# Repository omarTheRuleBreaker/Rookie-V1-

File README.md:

# Rookie-V1
Hi, I am making a cool Custom Keyboard from scratch, by myself

This is my custom 65% Alice layout keyboard that I’m designing from scratch. I started with watching some YOUTUBE videos and also took some help of AI for boosting up my Knowledge.

then I worked on schematic of the keyboard matrix, diodes, switches,  OLED display, Joystick, and the other components.
After finishing the schematic, I moved on to designing the PCB. I arranged the components, worked on the routing, and checked the connections and DRC errors to make sure everything was correct.

This project is helping me learn more about PCB design, KiCad, and how a keyboard actually works from the schematic to the final PCB.

### WHAT I LEARNED
Not gonna lie I learned many things it was a life time experience and next time I make an PCB for some other project it's  gonna be easy for me I learned shortcuts that will save me time and also made some friend's on SLACK that helped me , 
also #SHOUTOUT to @Flyingfish he saved me some time AND also THX to them who were  part of my journey.
- Here's what I really learned :
  
I learned how to turn a keyboard schematic into a proper PCB and how important it is to check every connection before moving forward. I also learned how to arrange components properly, route traces, use vias, and fix DRC errors in KiCad. Working on this project helped me understand more about PCB design and how all the different parts of a keyboard connect and work together.
gracias!

#### NOTE :-
If u want step by step PROCESS to make a simple easy Keyboard which include's Everything, SO just follow the  #### KEEB DOCS
HERE'S THE LINKE { https://keeb.hackclub.com/docs/getting-started/ }

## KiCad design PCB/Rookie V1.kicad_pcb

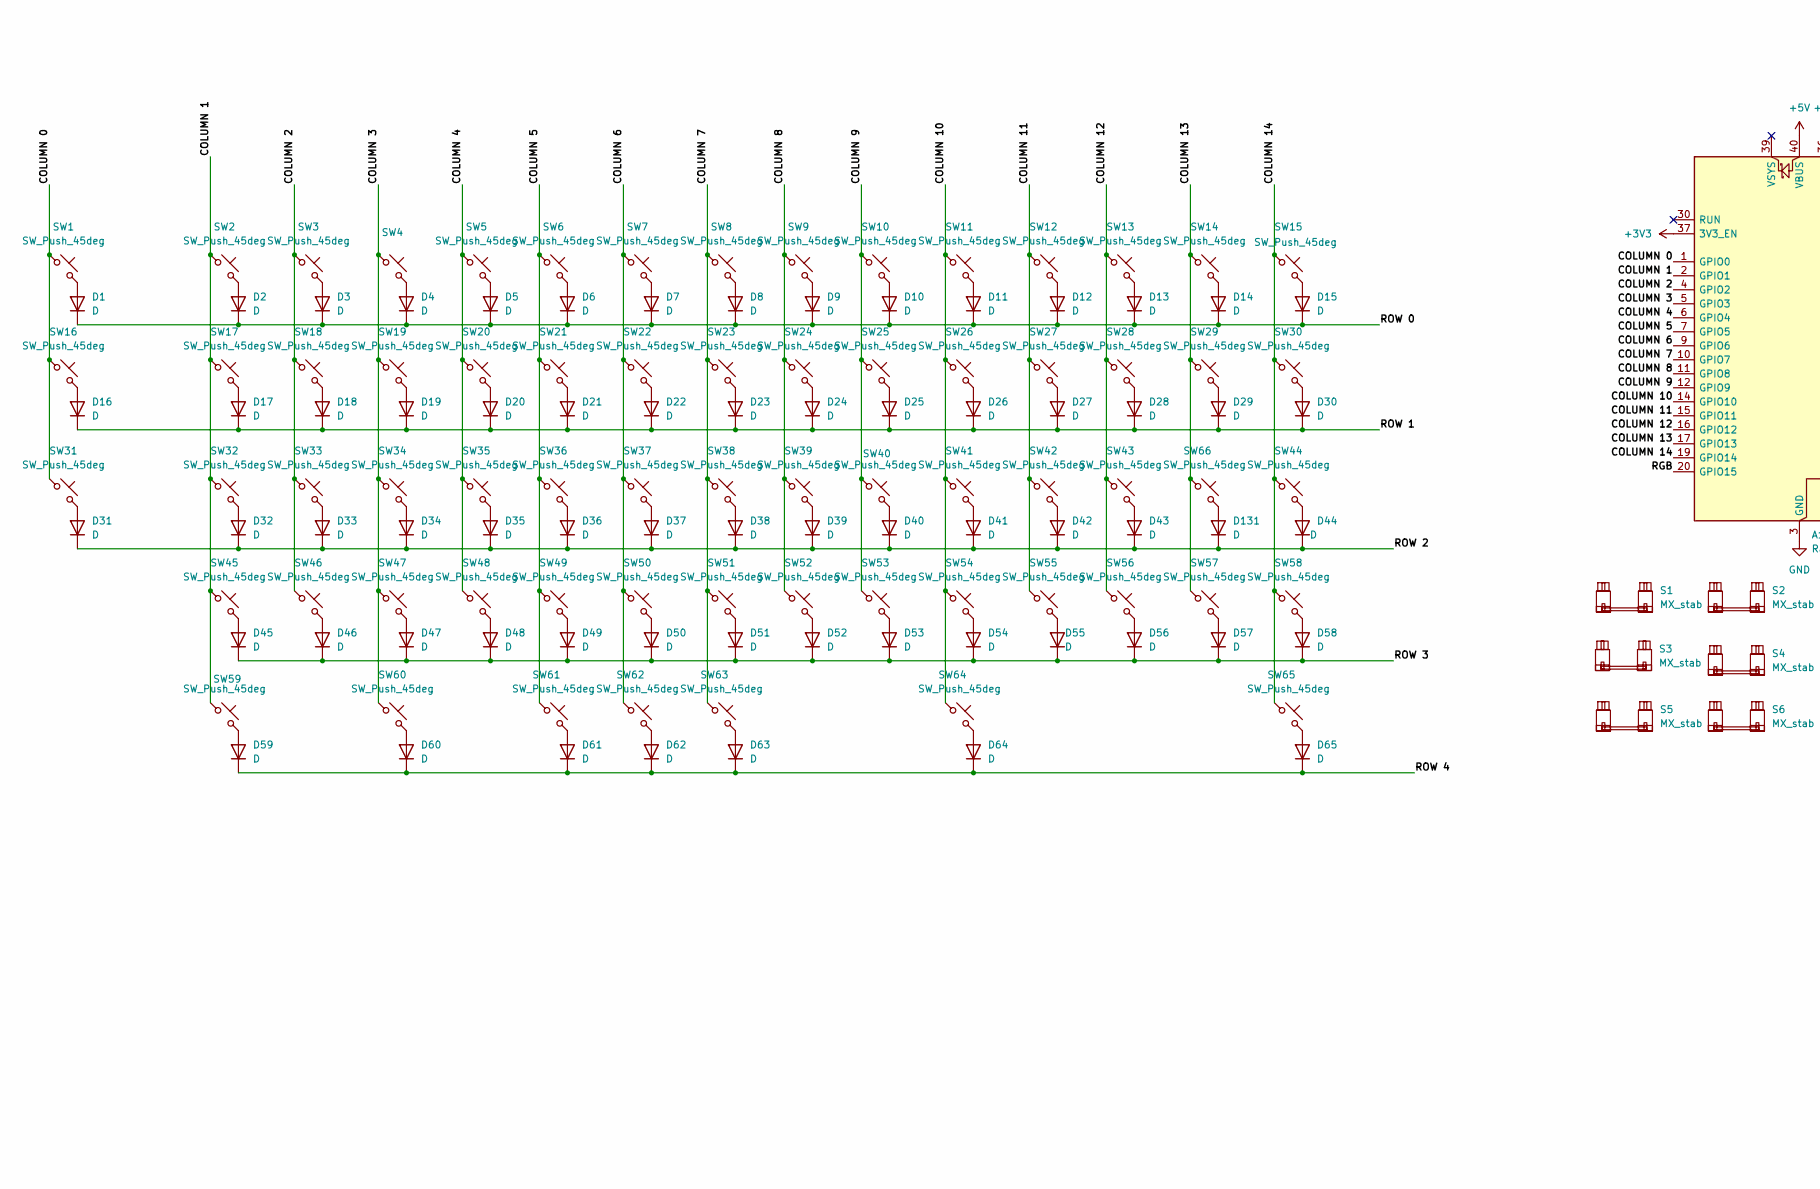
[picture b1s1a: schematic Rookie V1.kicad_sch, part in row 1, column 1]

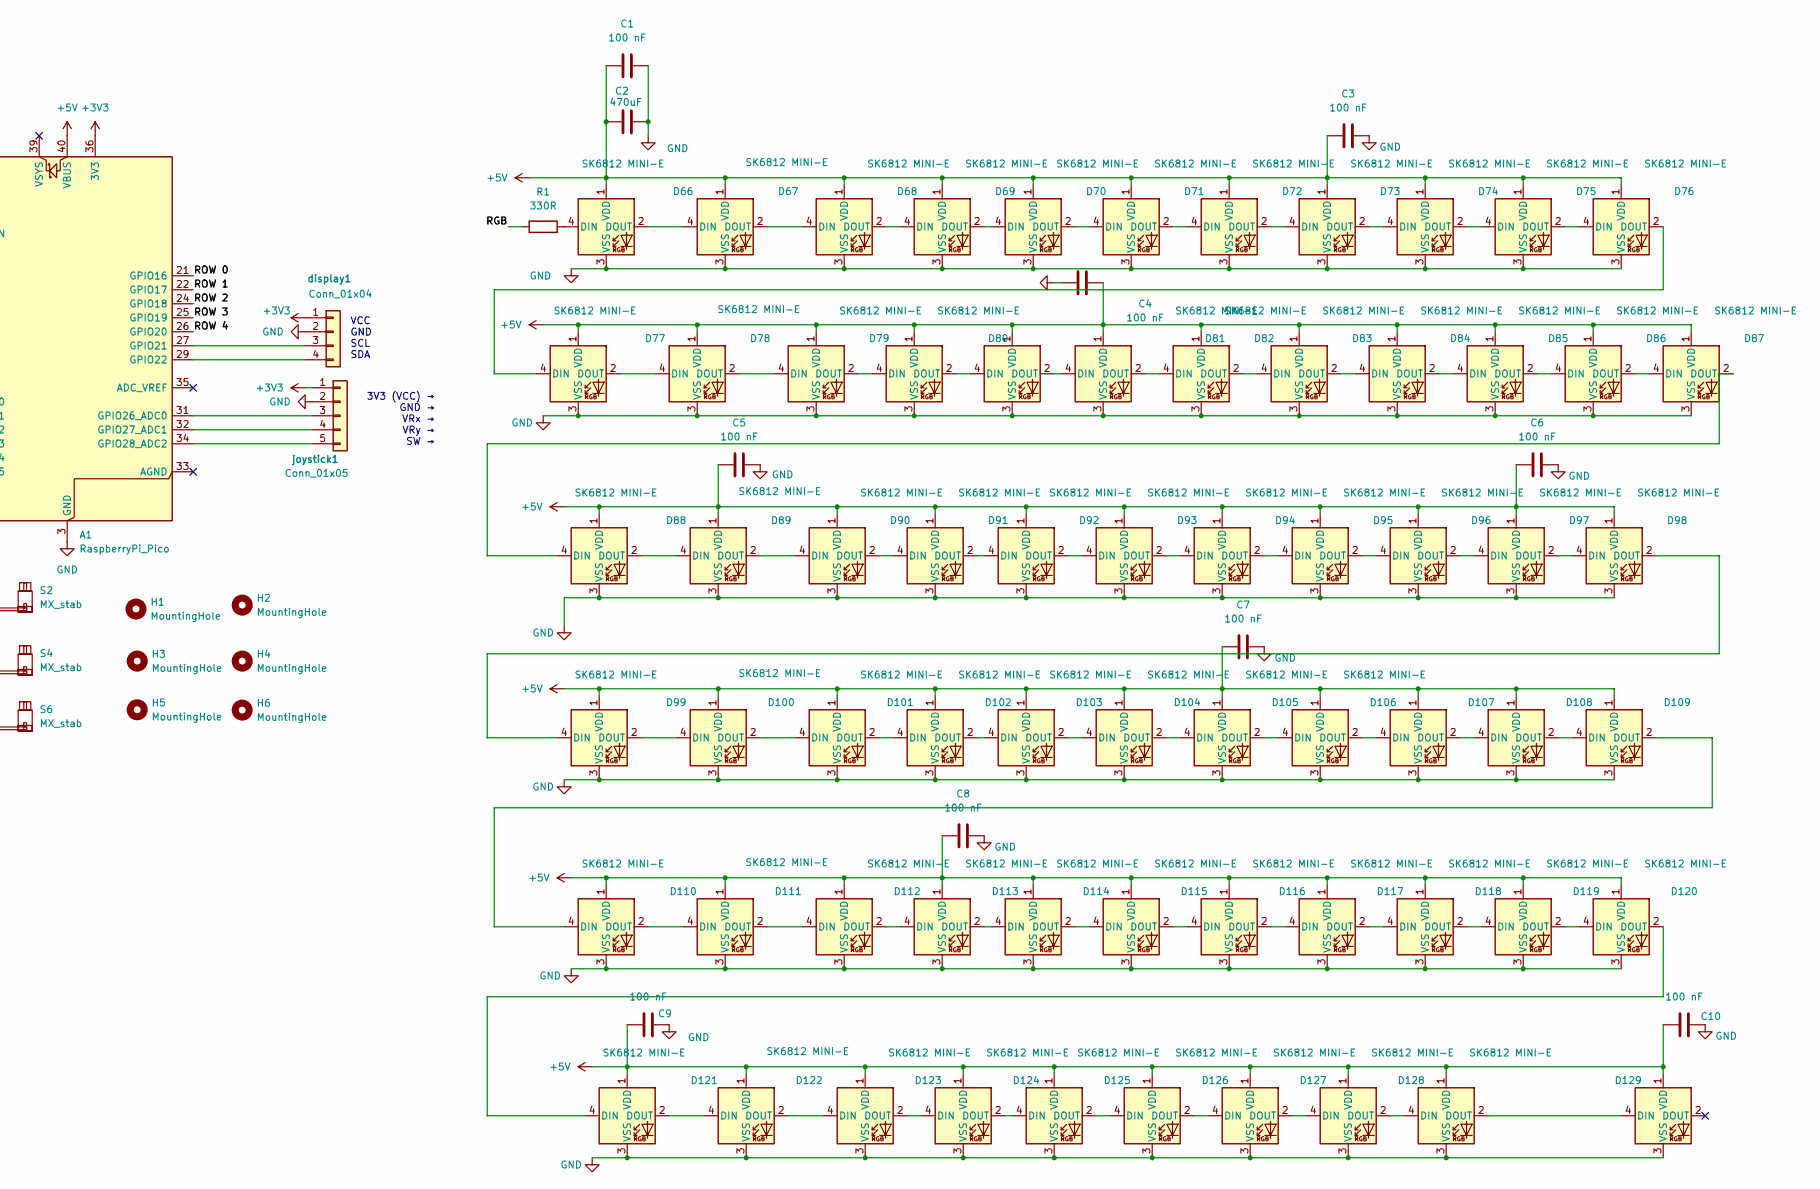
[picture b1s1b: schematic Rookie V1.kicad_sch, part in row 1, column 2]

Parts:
A1: RaspberryPi_Pico; RaspberryPi_Pico_Common_THT
C1, C3, C4, C5, C6, C7, C8, C9, C10: 100 nF; C_0603_1608Metric_Pad1.08x0.95mm_HandSolder
C2: 470uF; CP_EIA-7343-31_Kemet-D_HandSolder
D1, D2, D3, D4, D5, D6, D7, D8, D9, D10, D11, D12, D13, D14, D15, D16, D17, D18, D19, D20, D21, D22, D23, D24, D25, D26, D27, D28, D29, D30, D31, D32, D33, D34, D35, D36, D37, D38, D39, D40, D41, D42, D43, D44, D45, D46, D47, D48, D49, D50, D51, D52, D53, D54, D55, D56, D57, D58, D59, D60, D61, D62, D63, D64, D65, D131: D; D_SOD-123
D66, D67, D68, D69, D70, D71, D72, D73, D74, D75, D76, D77, D78, D79, D80, D81, D82, D83, D84, D85, D86, D87, D88, D89, D90, D91, D92, D93, D94, D95, D96, D97, D98, D99, D100, D101, D102, D103, D104, D105, D106, D107, D108, D109, D110, D111, D112, D113, D114, D115, D116, D117, D118, D119, D120, D121, D122, D123, D124, D125, D126, D127, D128, D129, D130, D132: SK6812 MINI-E; LED_SK6812MINI-E_3.2x2.8mm_P1.5mm_ReverseMount
H1, H2, H3, H4, H5, H6: MountingHole; MountingHole_3.2mm_M3
R1: 330R; R_0603_1608Metric_Pad0.98x0.95mm_HandSolder
S1: MX_stab; STAB_MX_P_2u
S2, S4, S5: MX_stab; STAB_MX_P_2.25u
S3, S6: MX_stab; STAB_MX_P_2.75u
SW1, SW2, SW3, SW5, SW6, SW7, SW8, SW9, SW10, SW11, SW12, SW13, SW14, SW15, SW16, SW18, SW19, SW20, SW21, SW22, SW23, SW24, SW25, SW26, SW27, SW28, SW29, SW30, SW31, SW33, SW34, SW35, SW36, SW37, SW38, SW39, SW40, SW41, SW42, SW43, SW44, SW45, SW46, SW47, SW48, SW49, SW50, SW51, SW52, SW53, SW54, SW55, SW56, SW57, SW58, SW61, SW62, SW63: SW_Push_45deg; SW_MX_HS_CPG151101S11_1u
SW4: SW_MX_HS_CPG151101S11_1u
SW17, SW66: SW_Push_45deg; SW_MX_HS_CPG151101S11_1.5u
SW32: SW_Push_45deg; SW_MX_HS_CPG151101S11_1.75u
SW59, SW60, SW64, SW65: SW_Push_45deg; SW_MX_HS_CPG151101S11_1.25u
display1: Conn_01x04; PinHeader_1x04_P2.54mm_Vertical
joystick1: Conn_01x05; PinHeader_1x05_P2.54mm_Vertical

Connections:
+3V3: A1.36 (3V3), A1.37 (3V3_EN), display1.1, joystick1.1
+5V: A1.40 (VBUS), C1.2, C2.1, C3.2, C4.1, C5.2, C6.2, C7.2, C8.2, C9.2, C10.2, D66.1 (VDD), D67.1 (VDD), D68.1 (VDD), D69.1 (VDD), D70.1 (VDD), D71.1 (VDD), D72.1 (VDD), D73.1 (VDD), D74.1 (VDD), D75.1 (VDD), D76.1 (VDD), D77.1 (VDD), D78.1 (VDD), D79.1 (VDD), D80.1 (VDD), D81.1 (VDD), D82.1 (VDD), D83.1 (VDD), D84.1 (VDD), D85.1 (VDD), D86.1 (VDD), D87.1 (VDD), D88.1 (VDD), D89.1 (VDD), D90.1 (VDD), D91.1 (VDD), D92.1 (VDD), D93.1 (VDD), D94.1 (VDD), D95.1 (VDD), D96.1 (VDD), D97.1 (VDD), D98.1 (VDD), D99.1 (VDD), D100.1 (VDD), D101.1 (VDD), D102.1 (VDD), D103.1 (VDD), D104.1 (VDD), D105.1 (VDD), D106.1 (VDD), D107.1 (VDD), D108.1 (VDD), D109.1 (VDD), D110.1 (VDD), D111.1 (VDD), D112.1 (VDD), D113.1 (VDD), D114.1 (VDD), D115.1 (VDD), D116.1 (VDD), D117.1 (VDD), D118.1 (VDD), D119.1 (VDD), D120.1 (VDD), D121.1 (VDD), D122.1 (VDD), D123.1 (VDD), D124.1 (VDD), D125.1 (VDD), D126.1 (VDD), D127.1 (VDD), D128.1 (VDD), D129.1 (VDD), D130.1 (VDD), D132.1 (VDD)
/COLUMN 0: A1.1 (GPIO0), SW1.1, SW16.1, SW31.1
/COLUMN 1: A1.2 (GPIO1), SW2.1, SW17.1, SW32.1, SW45.1, SW59.1
/COLUMN 2: A1.4 (GPIO2), SW3.1, SW18.1, SW33.1, SW46.1
/COLUMN 3: A1.5 (GPIO3), SW4.1, SW19.1, SW34.1, SW47.1, SW60.1
/COLUMN 4: A1.6 (GPIO4), SW5.1, SW20.1, SW35.1, SW48.1
/COLUMN 5: A1.7 (GPIO5), SW6.1, SW21.1, SW36.1, SW49.1, SW61.1
/COLUMN 6: A1.9 (GPIO6), SW7.1, SW22.1, SW37.1, SW50.1, SW62.1
/COLUMN 7: A1.10 (GPIO7), SW8.1, SW23.1, SW38.1, SW51.1, SW63.1
/COLUMN 8: A1.11 (GPIO8), SW9.1, SW24.1, SW39.1, SW52.1
/COLUMN 9: A1.12 (GPIO9), SW10.1, SW25.1, SW40.1, SW53.1
/COLUMN 10: A1.14 (GPIO10), SW11.1, SW26.1, SW41.1, SW54.1, SW64.1
/COLUMN 11: A1.15 (GPIO11), SW12.1, SW27.1, SW42.1, SW55.1
/COLUMN 12: A1.16 (GPIO12), SW13.1, SW28.1, SW43.1, SW56.1
/COLUMN 13: A1.17 (GPIO13), SW14.1, SW29.1, SW57.1, SW66.1
/COLUMN 14: A1.19 (GPIO14), SW15.1, SW30.1, SW44.1, SW58.1, SW65.1
/RGB: A1.20 (GPIO15), R1.1
/ROW 0: A1.21 (GPIO16), D1.1 (K), D2.1 (K), D3.1 (K), D4.1 (K), D5.1 (K), D6.1 (K), D7.1 (K), D8.1 (K), D9.1 (K), D10.1 (K), D11.1 (K), D12.1 (K), D13.1 (K), D14.1 (K), D15.1 (K)
/ROW 1: A1.22 (GPIO17), D16.1 (K), D17.1 (K), D18.1 (K), D19.1 (K), D20.1 (K), D21.1 (K), D22.1 (K), D23.1 (K), D24.1 (K), D25.1 (K), D26.1 (K), D27.1 (K), D28.1 (K), D29.1 (K), D30.1 (K)
/ROW 2: A1.24 (GPIO18), D31.1 (K), D32.1 (K), D33.1 (K), D34.1 (K), D35.1 (K), D36.1 (K), D37.1 (K), D38.1 (K), D39.1 (K), D40.1 (K), D41.1 (K), D42.1 (K), D43.1 (K), D44.1 (K), D131.1 (K)
/ROW 3: A1.25 (GPIO19), D45.1 (K), D46.1 (K), D47.1 (K), D48.1 (K), D49.1 (K), D50.1 (K), D51.1 (K), D52.1 (K), D53.1 (K), D54.1 (K), D55.1 (K), D56.1 (K), D57.1 (K), D58.1 (K)
/ROW 4: A1.26 (GPIO20), D59.1 (K), D60.1 (K), D61.1 (K), D62.1 (K), D63.1 (K), D64.1 (K), D65.1 (K)
GND: A1.3 (GND), A1.8 (GND), A1.13 (GND), A1.18 (GND), A1.23 (GND), A1.28 (GND), A1.38 (GND), C1.1, C2.2, C3.1, C4.2, C5.1, C6.1, C7.1, C8.1, C9.1, C10.1, D66.3 (VSS), D67.3 (VSS), D68.3 (VSS), D69.3 (VSS), D70.3 (VSS), D71.3 (VSS), D72.3 (VSS), D73.3 (VSS), D74.3 (VSS), D75.3 (VSS), D76.3 (VSS), D77.3 (VSS), D78.3 (VSS), D79.3 (VSS), D80.3 (VSS), D81.3 (VSS), D82.3 (VSS), D83.3 (VSS), D84.3 (VSS), D85.3 (VSS), D86.3 (VSS), D87.3 (VSS), D88.3 (VSS), D89.3 (VSS), D90.3 (VSS), D91.3 (VSS), D92.3 (VSS), D93.3 (VSS), D94.3 (VSS), D95.3 (VSS), D96.3 (VSS), D97.3 (VSS), D98.3 (VSS), D99.3 (VSS), D100.3 (VSS), D101.3 (VSS), D102.3 (VSS), D103.3 (VSS), D104.3 (VSS), D105.3 (VSS), D106.3 (VSS), D107.3 (VSS), D108.3 (VSS), D109.3 (VSS), D110.3 (VSS), D111.3 (VSS), D112.3 (VSS), D113.3 (VSS), D114.3 (VSS), D115.3 (VSS), D116.3 (VSS), D117.3 (VSS), D118.3 (VSS), D119.3 (VSS), D120.3 (VSS), D121.3 (VSS), D122.3 (VSS), D123.3 (VSS), D124.3 (VSS), D125.3 (VSS), D126.3 (VSS), D127.3 (VSS), D128.3 (VSS), D129.3 (VSS), D130.3 (VSS), D132.3 (VSS), display1.2, joystick1.2
unnamed: A1.27 (GPIO21), display1.3
unnamed: A1.29 (GPIO22), display1.4
unnamed: A1.31 (GPIO26_ADC0), joystick1.3
unnamed: A1.32 (GPIO27_ADC1), joystick1.4
unnamed: A1.34 (GPIO28_ADC2), joystick1.5
unnamed: D1.2 (A), SW1.2
unnamed: D2.2 (A), SW2.2
unnamed: D3.2 (A), SW3.2
unnamed: D4.2 (A), SW4.2
unnamed: D5.2 (A), SW5.2
unnamed: D6.2 (A), SW6.2
unnamed: D7.2 (A), SW7.2
unnamed: D8.2 (A), SW8.2
unnamed: D9.2 (A), SW9.2
unnamed: D10.2 (A), SW10.2
unnamed: D11.2 (A), SW11.2
unnamed: D12.2 (A), SW12.2
unnamed: D13.2 (A), SW13.2
unnamed: D14.2 (A), SW14.2
unnamed: D15.2 (A), SW15.2
unnamed: D16.2 (A), SW16.2
unnamed: D17.2 (A), SW17.2
unnamed: D18.2 (A), SW18.2
unnamed: D19.2 (A), SW19.2
unnamed: D20.2 (A), SW20.2
unnamed: D21.2 (A), SW21.2
unnamed: D22.2 (A), SW22.2
unnamed: D23.2 (A), SW23.2
unnamed: D24.2 (A), SW24.2
unnamed: D25.2 (A), SW25.2
unnamed: D26.2 (A), SW26.2
unnamed: D27.2 (A), SW27.2
unnamed: D28.2 (A), SW28.2
unnamed: D29.2 (A), SW29.2
unnamed: D30.2 (A), SW30.2
unnamed: D31.2 (A), SW31.2
unnamed: D32.2 (A), SW32.2
unnamed: D33.2 (A), SW33.2
unnamed: D34.2 (A), SW34.2
unnamed: D35.2 (A), SW35.2
unnamed: D36.2 (A), SW36.2
unnamed: D37.2 (A), SW37.2
unnamed: D38.2 (A), SW38.2
unnamed: D39.2 (A), SW39.2
unnamed: D40.2 (A), SW40.2
unnamed: D41.2 (A), SW41.2
unnamed: D42.2 (A), SW42.2
unnamed: D43.2 (A), SW43.2
unnamed: D44.2 (A), SW44.2
unnamed: D45.2 (A), SW45.2
unnamed: D46.2 (A), SW46.2
unnamed: D47.2 (A), SW47.2
unnamed: D48.2 (A), SW48.2
unnamed: D49.2 (A), SW49.2
unnamed: D50.2 (A), SW50.2
unnamed: D51.2 (A), SW51.2
unnamed: D52.2 (A), SW52.2
unnamed: D53.2 (A), SW53.2
unnamed: D54.2 (A), SW54.2
unnamed: D55.2 (A), SW55.2
unnamed: D56.2 (A), SW56.2
unnamed: D57.2 (A), SW57.2
unnamed: D58.2 (A), SW58.2
unnamed: D59.2 (A), SW59.2
unnamed: D60.2 (A), SW60.2
unnamed: D61.2 (A), SW61.2
unnamed: D62.2 (A), SW62.2
unnamed: D63.2 (A), SW63.2
unnamed: D64.2 (A), SW64.2
unnamed: D65.2 (A), SW65.2
unnamed: D66.4 (DIN), R1.2
unnamed: D66.2 (DOUT), D67.4 (DIN)
unnamed: D67.2 (DOUT), D68.4 (DIN)
unnamed: D68.2 (DOUT), D69.4 (DIN)
unnamed: D69.2 (DOUT), D70.4 (DIN)
unnamed: D70.2 (DOUT), D71.4 (DIN)
unnamed: D71.2 (DOUT), D72.4 (DIN)
unnamed: D72.2 (DOUT), D73.4 (DIN)
unnamed: D73.2 (DOUT), D74.4 (DIN)
unnamed: D74.2 (DOUT), D75.4 (DIN)
unnamed: D75.2 (DOUT), D76.4 (DIN)
unnamed: D76.2 (DOUT), D77.4 (DIN)
unnamed: D77.2 (DOUT), D78.4 (DIN)
unnamed: D78.2 (DOUT), D79.4 (DIN)
unnamed: D79.2 (DOUT), D80.4 (DIN)
unnamed: D81.2 (DOUT), D82.4 (DIN)
unnamed: D82.2 (DOUT), D83.4 (DIN)
unnamed: D83.2 (DOUT), D84.4 (DIN)
unnamed: D84.2 (DOUT), D85.4 (DIN)
unnamed: D85.2 (DOUT), D86.4 (DIN)
unnamed: D86.2 (DOUT), D87.4 (DIN)
unnamed: D87.2 (DOUT), D88.4 (DIN)
unnamed: D88.2 (DOUT), D89.4 (DIN)
unnamed: D89.2 (DOUT), D90.4 (DIN)
unnamed: D90.2 (DOUT), D91.4 (DIN)
unnamed: D91.2 (DOUT), D92.4 (DIN)
unnamed: D92.2 (DOUT), D93.4 (DIN)
unnamed: D93.2 (DOUT), D94.4 (DIN)
unnamed: D94.2 (DOUT), D95.4 (DIN)
unnamed: D95.2 (DOUT), D96.4 (DIN)
unnamed: D96.2 (DOUT), D97.4 (DIN)
unnamed: D97.2 (DOUT), D98.4 (DIN)
unnamed: D98.2 (DOUT), D99.4 (DIN)
unnamed: D99.2 (DOUT), D100.4 (DIN)
unnamed: D100.2 (DOUT), D101.4 (DIN)
unnamed: D101.2 (DOUT), D102.4 (DIN)
unnamed: D102.2 (DOUT), D103.4 (DIN)
unnamed: D103.2 (DOUT), D104.4 (DIN)
unnamed: D104.2 (DOUT), D105.4 (DIN)
unnamed: D105.2 (DOUT), D106.4 (DIN)
unnamed: D106.2 (DOUT), D107.4 (DIN)
unnamed: D107.2 (DOUT), D108.4 (DIN)
unnamed: D108.2 (DOUT), D109.4 (DIN)
unnamed: D109.2 (DOUT), D110.4 (DIN)
unnamed: D110.2 (DOUT), D111.4 (DIN)
unnamed: D111.2 (DOUT), D112.4 (DIN)
unnamed: D112.2 (DOUT), D113.4 (DIN)
unnamed: D113.2 (DOUT), D114.4 (DIN)
unnamed: D114.2 (DOUT), D115.4 (DIN)
unnamed: D115.2 (DOUT), D116.4 (DIN)
unnamed: D116.2 (DOUT), D117.4 (DIN)
unnamed: D117.2 (DOUT), D118.4 (DIN)
unnamed: D118.2 (DOUT), D119.4 (DIN)
unnamed: D119.2 (DOUT), D120.4 (DIN)
unnamed: D120.2 (DOUT), D121.4 (DIN)
unnamed: D121.2 (DOUT), D122.4 (DIN)
unnamed: D122.2 (DOUT), D123.4 (DIN)
unnamed: D123.2 (DOUT), D124.4 (DIN)
unnamed: D124.2 (DOUT), D125.4 (DIN)
unnamed: D125.2 (DOUT), D126.4 (DIN)
unnamed: D126.2 (DOUT), D127.4 (DIN)
unnamed: D127.2 (DOUT), D128.4 (DIN)
unnamed: D128.2 (DOUT), D129.4 (DIN)
unnamed: D129.2 (DOUT), D130.4 (DIN)
unnamed: D131.2 (A), SW66.2
unnamed: D80.2 (DOUT), D132.4 (DIN)
unnamed: D81.4 (DIN), D132.2 (DOUT)

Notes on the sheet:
3V3 (VCC) → GND → VRx → VRy → SW →
VCC GND SCL SDA

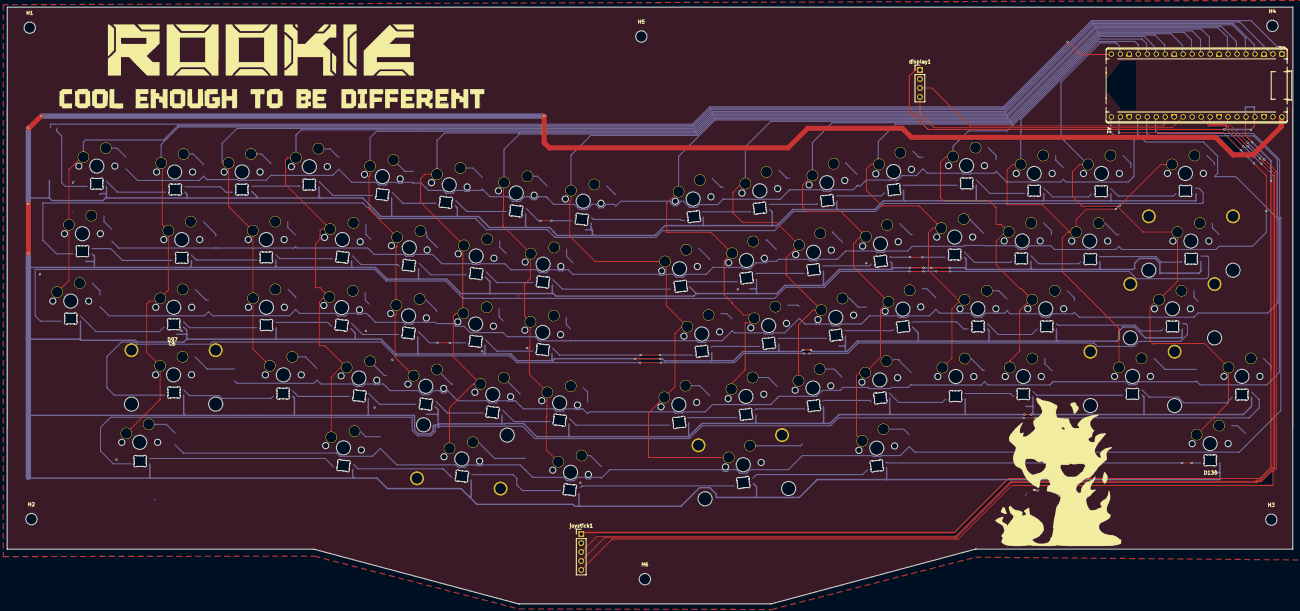
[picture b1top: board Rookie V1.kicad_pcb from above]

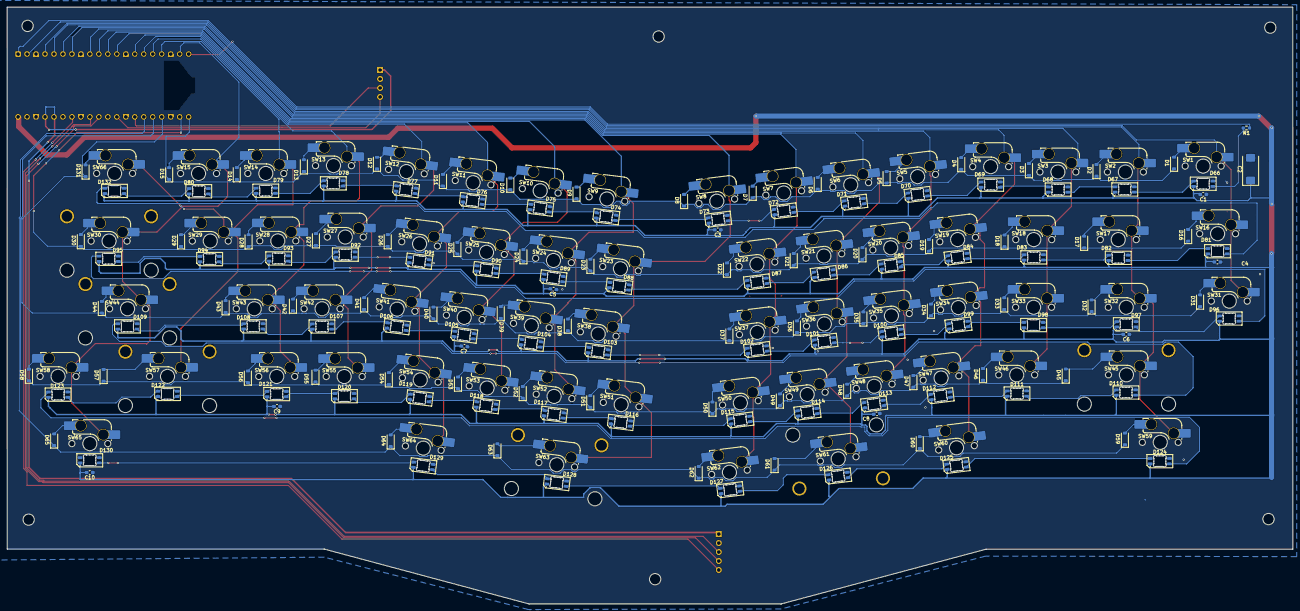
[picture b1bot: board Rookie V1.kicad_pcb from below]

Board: 2 copper layers, 363.7 x 168.8 mm, 225 parts (210 on the bottom side), 161 nets.

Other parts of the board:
aaaaaaaa: LOGO; MM
